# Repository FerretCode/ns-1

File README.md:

# ns-1

Lo-fi first hardware sampler

# Overview

- Teensy 4.1 based
- 16 Cherry MX switch pads
- 1/4" line in/out
- 3.5mm headphone jack
- 3 rotary encoders for sample editing
- 4 potentiometers for FX control
- Slider for master track volume control
- MicroSD card for loading and exporting samples
- Per-pad looping
- Resampling
- Sampling over USB-C

## Architecture

- The core audio processing functionality is provided by the Teensy 4.1 and its accompanying audio shield (Rev. D)
- Adafruit 1.9" TFT display over SPI
- Line in/out, headphone jack is handled by the audio shield, with volume control in firmware

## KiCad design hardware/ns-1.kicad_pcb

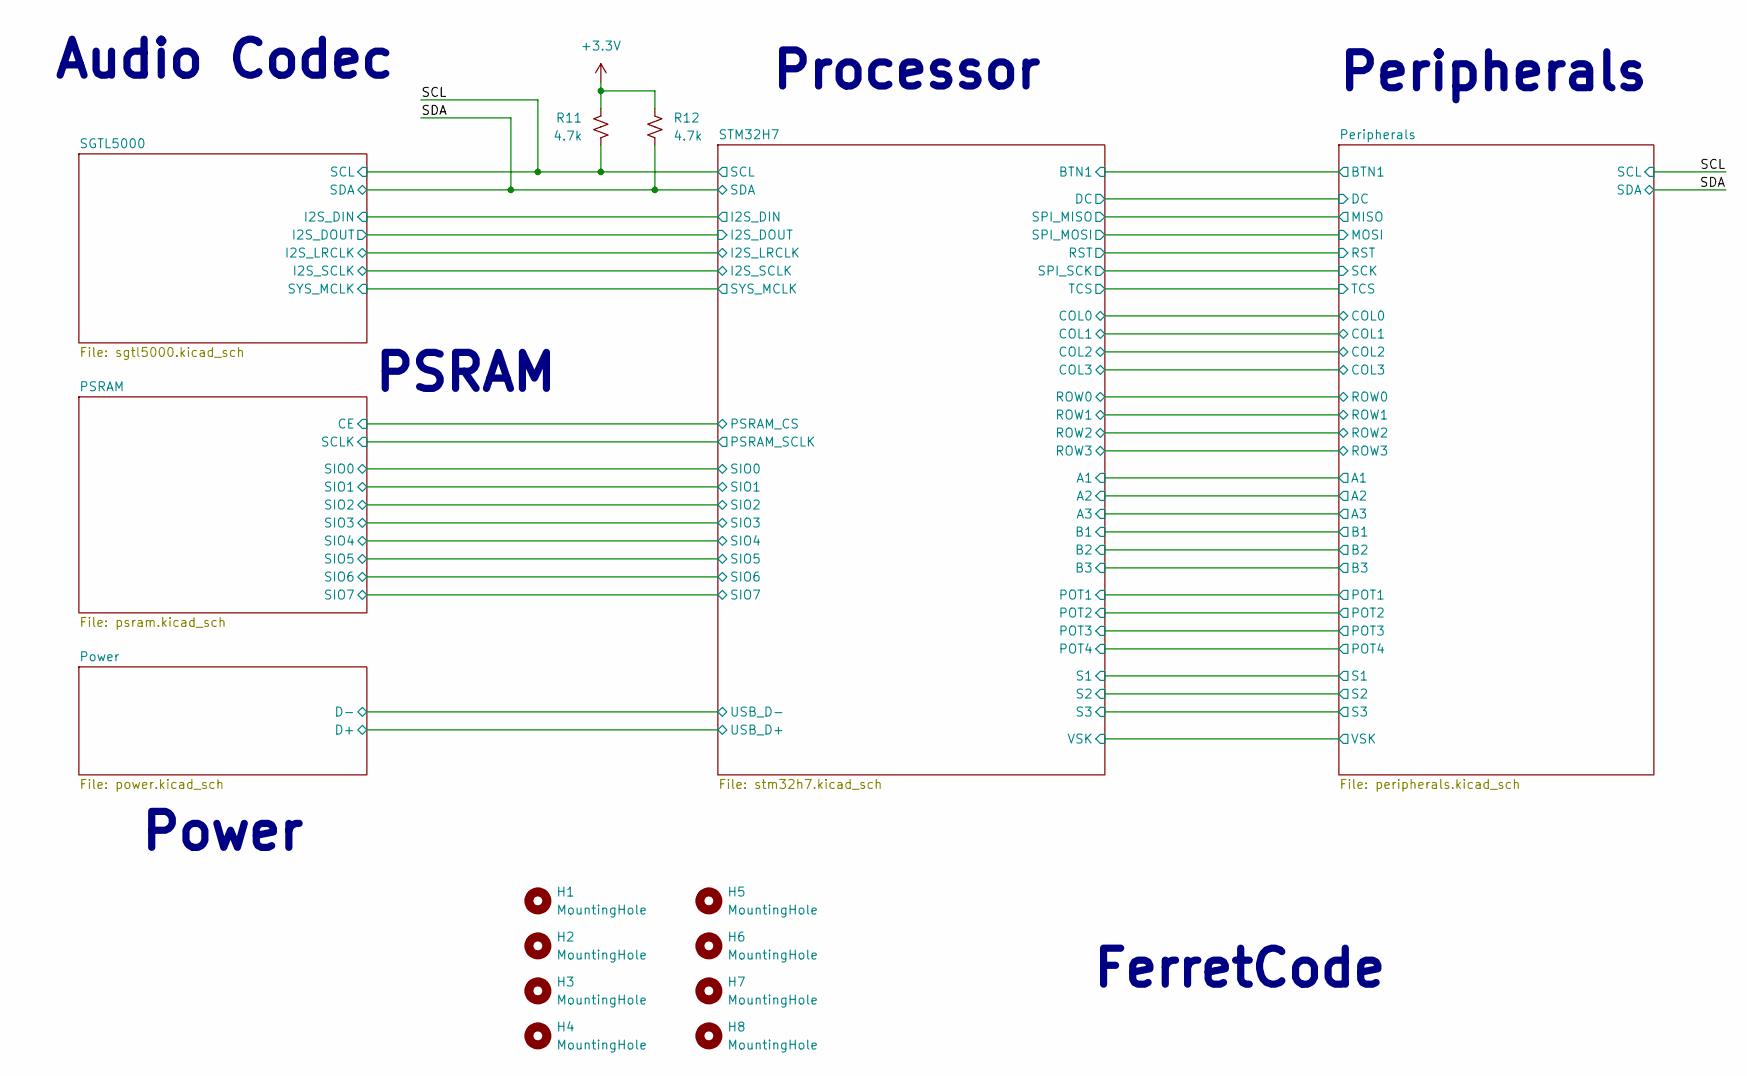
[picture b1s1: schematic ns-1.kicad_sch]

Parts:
H1, H2, H3, H4: MountingHole; MountingHole_2.5mm
H5, H6, H7, H8: MountingHole; MountingHole_4.5mm
R11, R12: 4.7k; R_0402_1005Metric; LCSC PN C25900

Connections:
+3.3V: R11.1, R12.1; also elsewhere on the board
/SCL: R11.2; also elsewhere on the board
/SDA: R12.2; also elsewhere on the board

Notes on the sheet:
Processor
FerretCode
Power
Peripherals
Audio Codec
PSRAM

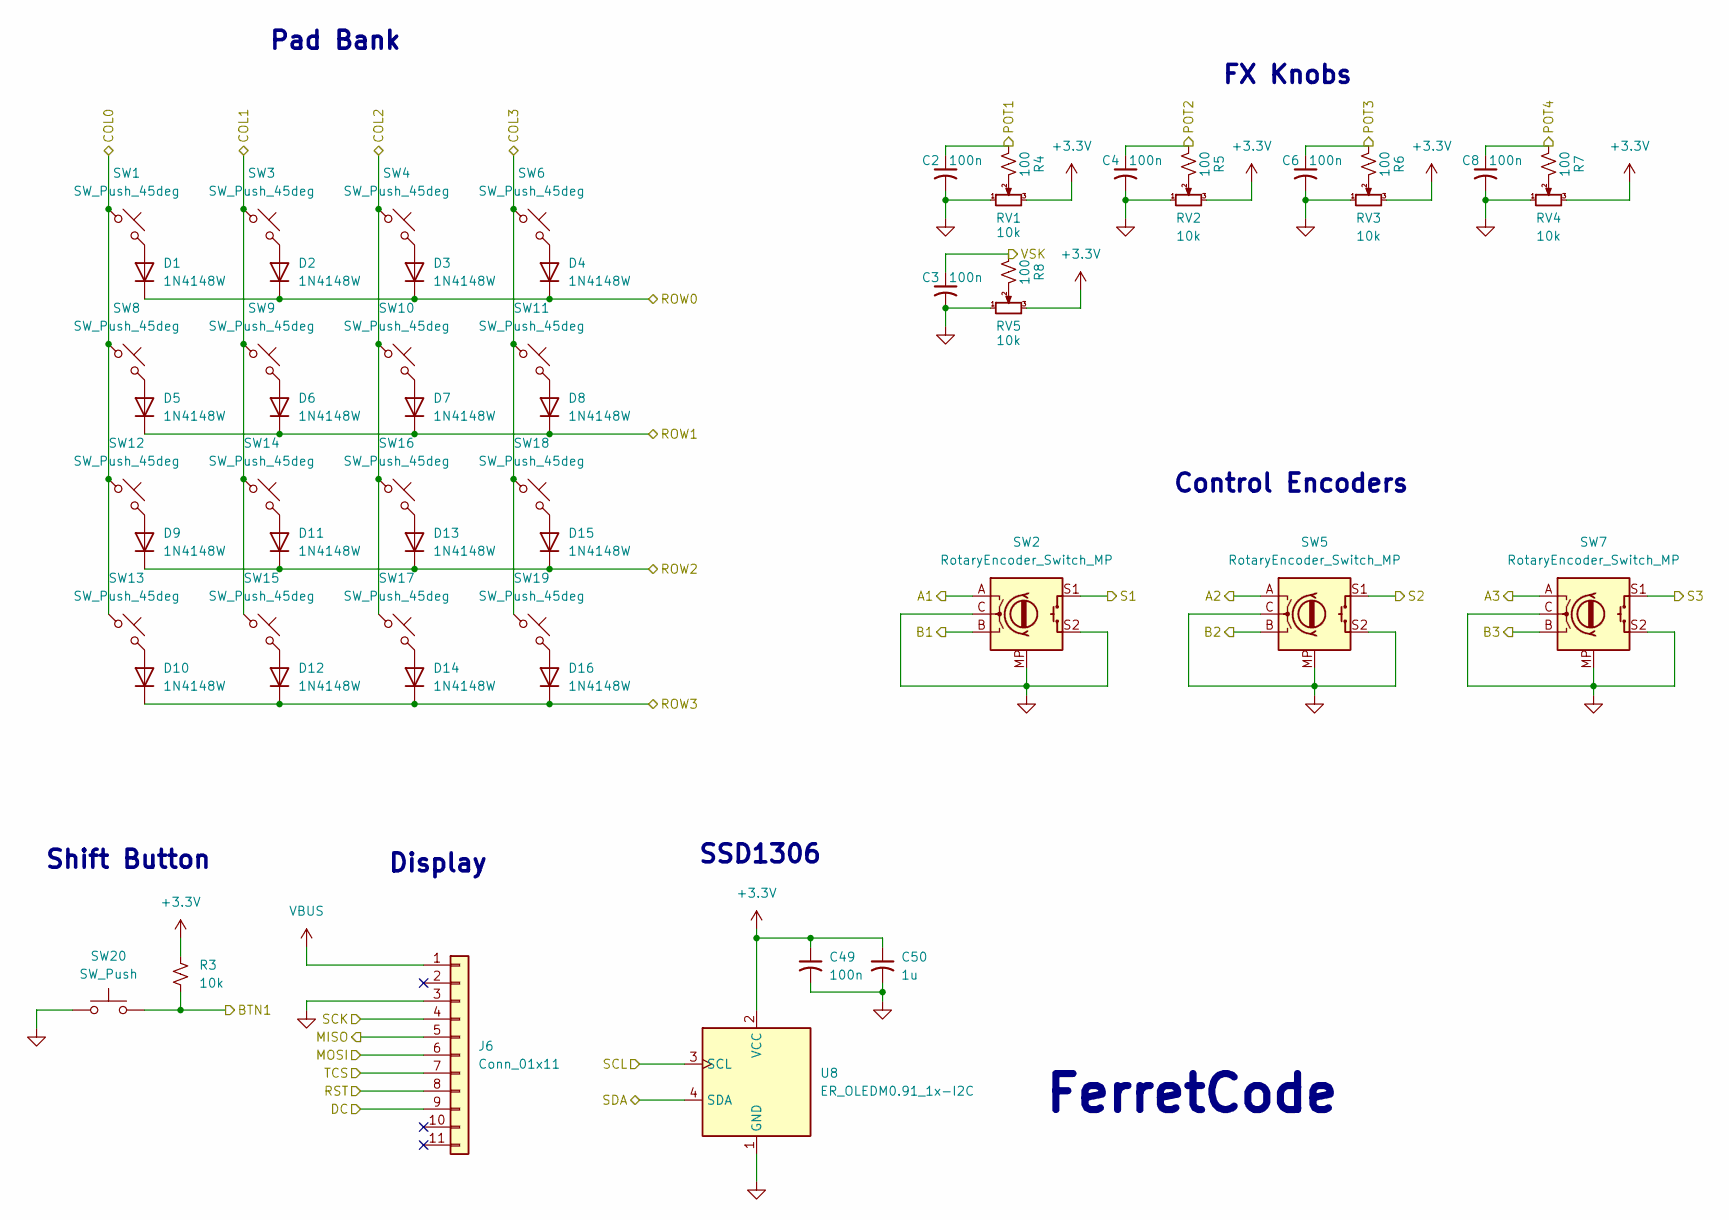
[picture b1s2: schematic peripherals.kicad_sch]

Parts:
C2, C3, C4, C6: 100n; C_0402_1005Metric; LCSC PN C22435941
C8, C49: 100n; C_0402_1005Metric; LCSC PN C1525
C50: 1u; C_0402_1005Metric; LCSC PN C52923
D1, D2, D3, D4, D5, D6, D7, D8, D9, D10, D11, D12, D13, D14, D15, D16: 1N4148W; D_SOD-123; LCSC PN C917030
J6: Conn_01x11; PinHeader_1x11_P2.54mm_Vertical
R3: 10k; R_0603_1608Metric; LCSC PN C25804
R4, R5, R6, R7, R8: 100; R_0603_1608Metric; LCSC PN C122970
RV1, RV2, RV3, RV4, RV5: 10k; Potentiometer_Alps_RK09K_Single_Vertical
SW1, SW3, SW4, SW6, SW8, SW9, SW10, SW11, SW12, SW13, SW14, SW15, SW16, SW17, SW18, SW19: SW_Push_45deg; SW_Cherry_MX_1.00u_PCB
SW2, SW5, SW7: RotaryEncoder_Switch_MP; RotaryEncoder_Alps_EC11E-Switch_Vertical_H20mm
SW20: SW_Push; SW_Cherry_MX_1.00u_PCB
U8: ER_OLEDM0.91_1x-I2C

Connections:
+3.3V: C49.1, C50.1, R3.1, RV1.3, RV2.3, RV3.3, RV4.3, RV5.3, U8.2 (VCC); also elsewhere on the board
/Peripherals/A1: SW2.A; also elsewhere on the board
/Peripherals/A2: SW5.A; also elsewhere on the board
/Peripherals/A3: SW7.A; also elsewhere on the board
/Peripherals/B1: SW2.B; also elsewhere on the board
/Peripherals/B2: SW5.B; also elsewhere on the board
/Peripherals/B3: SW7.B; also elsewhere on the board
/Peripherals/BTN1: R3.2, SW20.2; also elsewhere on the board
/Peripherals/COL0: SW1.1, SW8.1, SW12.1, SW13.1; also elsewhere on the board
/Peripherals/COL1: SW3.1, SW9.1, SW14.1, SW15.1; also elsewhere on the board
/Peripherals/COL2: SW4.1, SW10.1, SW16.1, SW17.1; also elsewhere on the board
/Peripherals/COL3: SW6.1, SW11.1, SW18.1, SW19.1; also elsewhere on the board
/Peripherals/DC: J6.9; also elsewhere on the board
/Peripherals/MISO: J6.5; also elsewhere on the board
/Peripherals/MOSI: J6.6; also elsewhere on the board
/Peripherals/POT1: C2.1, R4.2; also elsewhere on the board
/Peripherals/POT2: C4.1, R5.2; also elsewhere on the board
/Peripherals/POT3: C6.1, R6.2; also elsewhere on the board
/Peripherals/POT4: C8.1, R7.2; also elsewhere on the board
/Peripherals/ROW0: D1.1 (K), D2.1 (K), D3.1 (K), D4.1 (K); also elsewhere on the board
/Peripherals/ROW1: D5.1 (K), D6.1 (K), D7.1 (K), D8.1 (K); also elsewhere on the board
/Peripherals/ROW2: D9.1 (K), D11.1 (K), D13.1 (K), D15.1 (K); also elsewhere on the board
/Peripherals/ROW3: D10.1 (K), D12.1 (K), D14.1 (K), D16.1 (K); also elsewhere on the board
/Peripherals/RST: J6.8; also elsewhere on the board
/Peripherals/S1: SW2.S1; also elsewhere on the board
/Peripherals/S2: SW5.S1; also elsewhere on the board
/Peripherals/S3: SW7.S1; also elsewhere on the board
/Peripherals/SCK: J6.4; also elsewhere on the board
/Peripherals/TCS: J6.7; also elsewhere on the board
/Peripherals/VSK: C3.1, R8.2; also elsewhere on the board
/SCL: U8.3 (SCL); also elsewhere on the board
/SDA: U8.4 (SDA); also elsewhere on the board
GND: C2.2, C3.2, C4.2, C6.2, C8.2, C49.2, C50.2, J6.3, RV1.1, RV2.1, RV3.1, RV4.1, RV5.1, SW2.C, SW2.MP, SW2.S2, SW5.C, SW5.MP, SW5.S2, SW7.C, SW7.MP, SW7.S2, SW20.1, U8.1 (GND); also elsewhere on the board
unnamed: D1.2 (A), SW1.2
unnamed: D2.2 (A), SW3.2
unnamed: D3.2 (A), SW4.2
unnamed: D4.2 (A), SW6.2
unnamed: D5.2 (A), SW8.2
unnamed: D6.2 (A), SW9.2
unnamed: D7.2 (A), SW10.2
unnamed: D8.2 (A), SW11.2
unnamed: D9.2 (A), SW12.2
unnamed: D10.2 (A), SW13.2
unnamed: D11.2 (A), SW14.2
unnamed: D12.2 (A), SW15.2
unnamed: D13.2 (A), SW16.2
unnamed: D14.2 (A), SW17.2
unnamed: D15.2 (A), SW18.2
unnamed: D16.2 (A), SW19.2
unnamed: R4.1, RV1.2
unnamed: R5.1, RV2.2
unnamed: R6.1, RV3.2
unnamed: R7.1, RV4.2
unnamed: R8.1, RV5.2
VBUS: J6.1; also elsewhere on the board

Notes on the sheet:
FerretCode
FX Knobs
Display
SSD1306
Pad Bank
Control Encoders
Shift Button

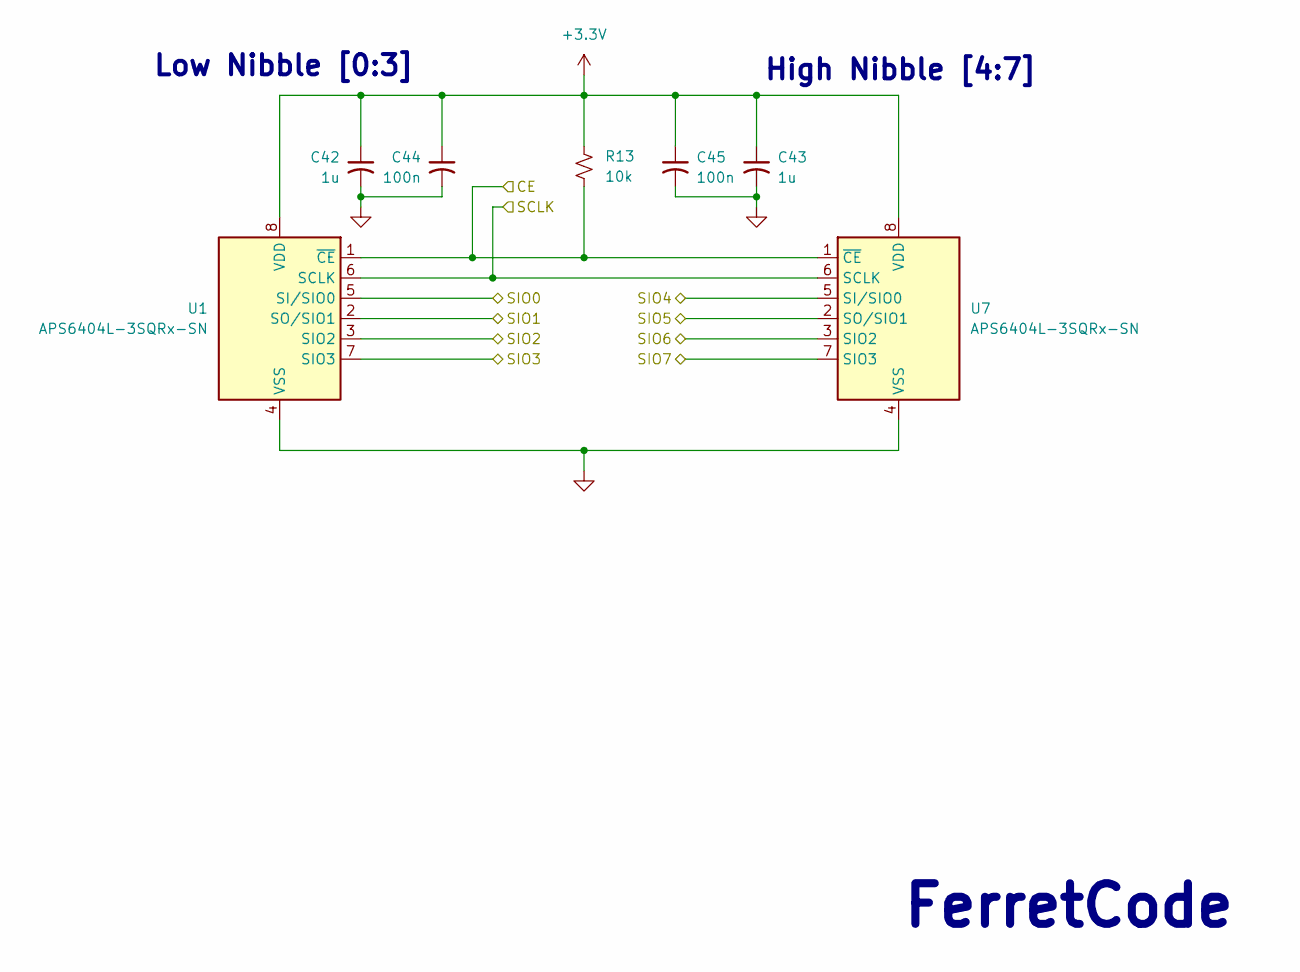
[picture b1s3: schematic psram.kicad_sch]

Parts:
C42, C43: 1u; C_0402_1005Metric; LCSC PN C52923
C44, C45: 100n; C_0402_1005Metric; LCSC PN C1525
R13: 10k; R_0402_1005Metric; LCSC PN C25744
U1, U7: APS6404L-3SQRx-SN; SOIC-8_3.9x4.9mm_P1.27mm; LCSC PN C3028887

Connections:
+3.3V: C42.1, C43.1, C44.1, C45.1, R13.1, U1.8 (VDD), U7.8 (VDD); also elsewhere on the board
/PSRAM/CE: R13.2, U1.1 (~CE), U7.1 (~CE); also elsewhere on the board
/PSRAM/SCLK: U1.6 (SCLK), U7.6 (SCLK); also elsewhere on the board
/PSRAM/SIO0: U1.5 (SI/SIO0); also elsewhere on the board
/PSRAM/SIO1: U1.2 (SO/SIO1); also elsewhere on the board
/PSRAM/SIO2: U1.3 (SIO2); also elsewhere on the board
/PSRAM/SIO3: U1.7 (SIO3); also elsewhere on the board
/PSRAM/SIO4: U7.5 (SI/SIO0); also elsewhere on the board
/PSRAM/SIO5: U7.2 (SO/SIO1); also elsewhere on the board
/PSRAM/SIO6: U7.3 (SIO2); also elsewhere on the board
/PSRAM/SIO7: U7.7 (SIO3); also elsewhere on the board
GND: C42.2, C43.2, C44.2, C45.2, U1.4 (VSS), U7.4 (VSS); also elsewhere on the board

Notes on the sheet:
FerretCode
Low Nibble [0:3]
High Nibble [4:7]

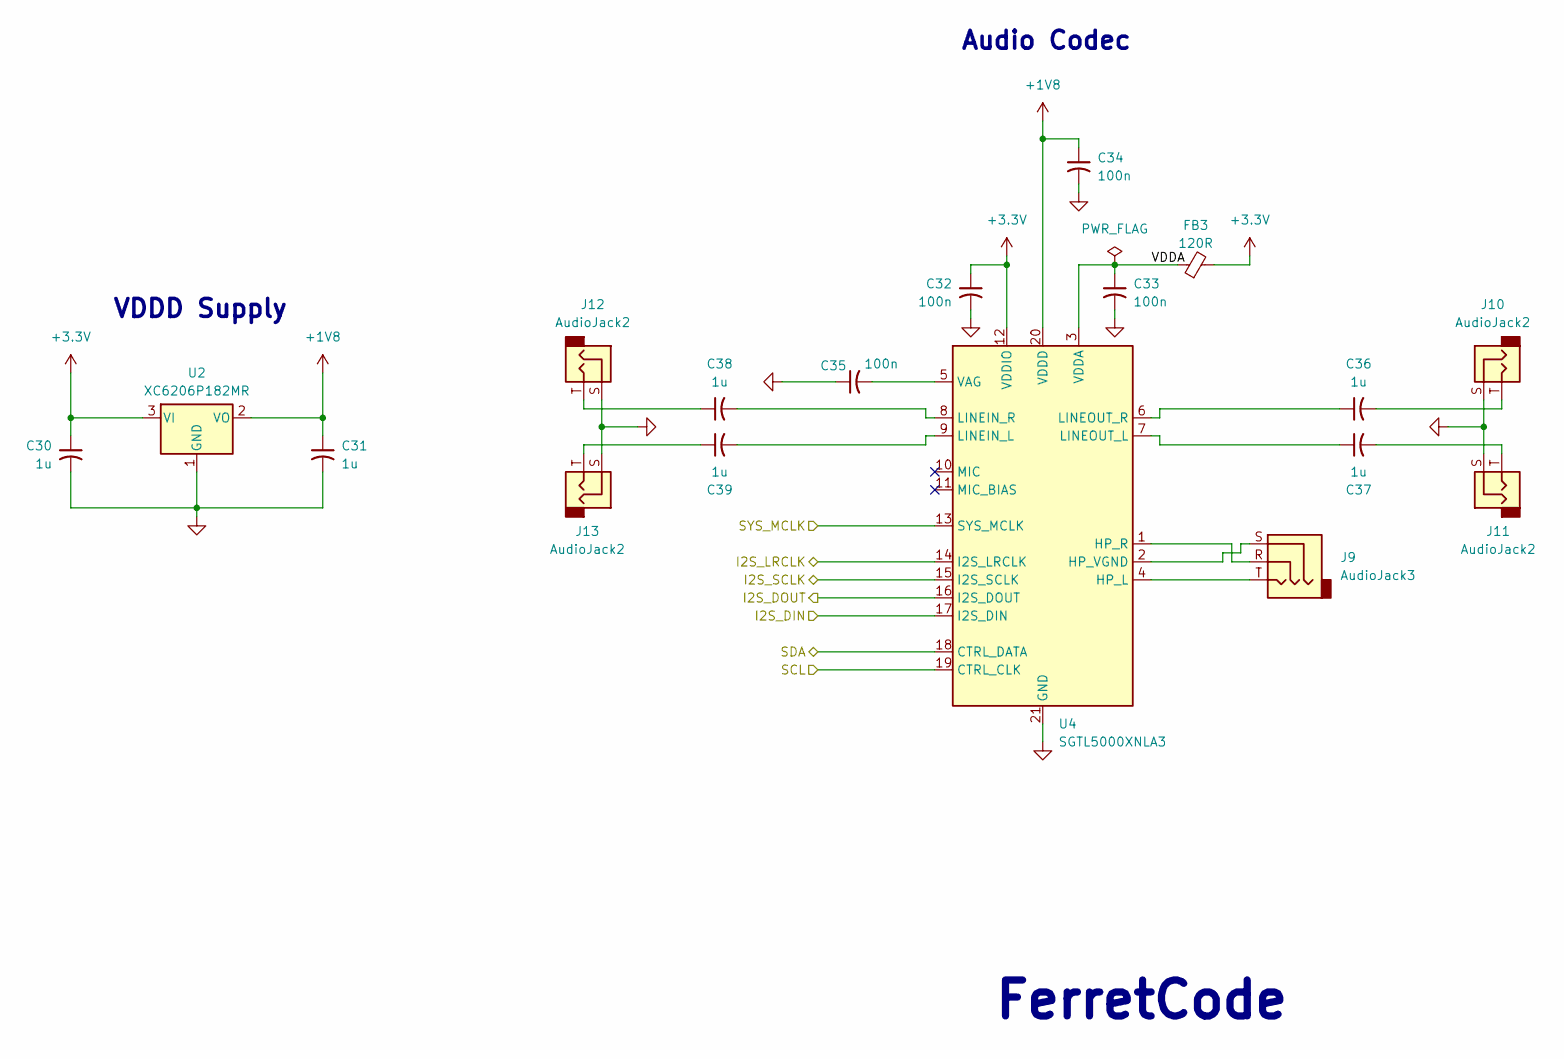
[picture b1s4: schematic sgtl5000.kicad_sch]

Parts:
C30, C31, C36, C37, C38, C39: 1u; C_0402_1005Metric; LCSC PN C52923
C32, C33, C34, C35: 100n; C_0402_1005Metric; LCSC PN C1525
FB3: 120R; L_0603_1608Metric; LCSC PN C14709
J9: AudioJack3; Jack_3.5mm_CUI_SJ-3523-SMT_Horizontal
J10, J11, J12, J13: AudioJack2; Jack_6.35mm_Neutrik_NRJ4HF_Horizontal
U2: XC6206P182MR; SOT-23-3; LCSC PN C347373
U4: SGTL5000XNLA3; QFN-20-1EP_3x3mm_P0.4mm_EP1.65x1.65mm; LCSC PN C2651833

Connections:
+1V8: C31.1, C34.1, U2.2 (VO), U4.20 (VDDD)
+3.3V: C30.1, C32.1, FB3.2, U2.3 (VI), U4.12 (VDDIO); also elsewhere on the board
/SCL: U4.19 (CTRL_CLK); also elsewhere on the board
/SDA: U4.18 (CTRL_DATA); also elsewhere on the board
/SGTL5000/I2S_DIN: U4.17 (I2S_DIN); also elsewhere on the board
/SGTL5000/I2S_DOUT: U4.16 (I2S_DOUT); also elsewhere on the board
/SGTL5000/I2S_LRCLK: U4.14 (I2S_LRCLK); also elsewhere on the board
/SGTL5000/I2S_SCLK: U4.15 (I2S_SCLK); also elsewhere on the board
/SGTL5000/SYS_MCLK: U4.13 (SYS_MCLK); also elsewhere on the board
/SGTL5000/VDDA: C33.1, FB3.1, U4.3 (VDDA)
GND: C30.2, C31.2, C32.2, C33.2, C34.2, C35.1, J10.S, J11.S, J12.S, J13.S, U2.1 (GND), U4.21 (GND); also elsewhere on the board
unnamed: C36.2, J10.T
unnamed: C37.2, J11.T
unnamed: C38.1, J12.T
unnamed: C39.1, J13.T
unnamed: J9.T, U4.4 (HP_L)
unnamed: J9.R, U4.1 (HP_R)
unnamed: J9.S, U4.2 (HP_VGND)
unnamed: C39.2, U4.9 (LINEIN_L)
unnamed: C38.2, U4.8 (LINEIN_R)
unnamed: C37.1, U4.7 (LINEOUT_L)
unnamed: C36.1, U4.6 (LINEOUT_R)
unnamed: C35.2, U4.5 (VAG)

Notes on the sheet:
VDDD Supply
Audio Codec
FerretCode

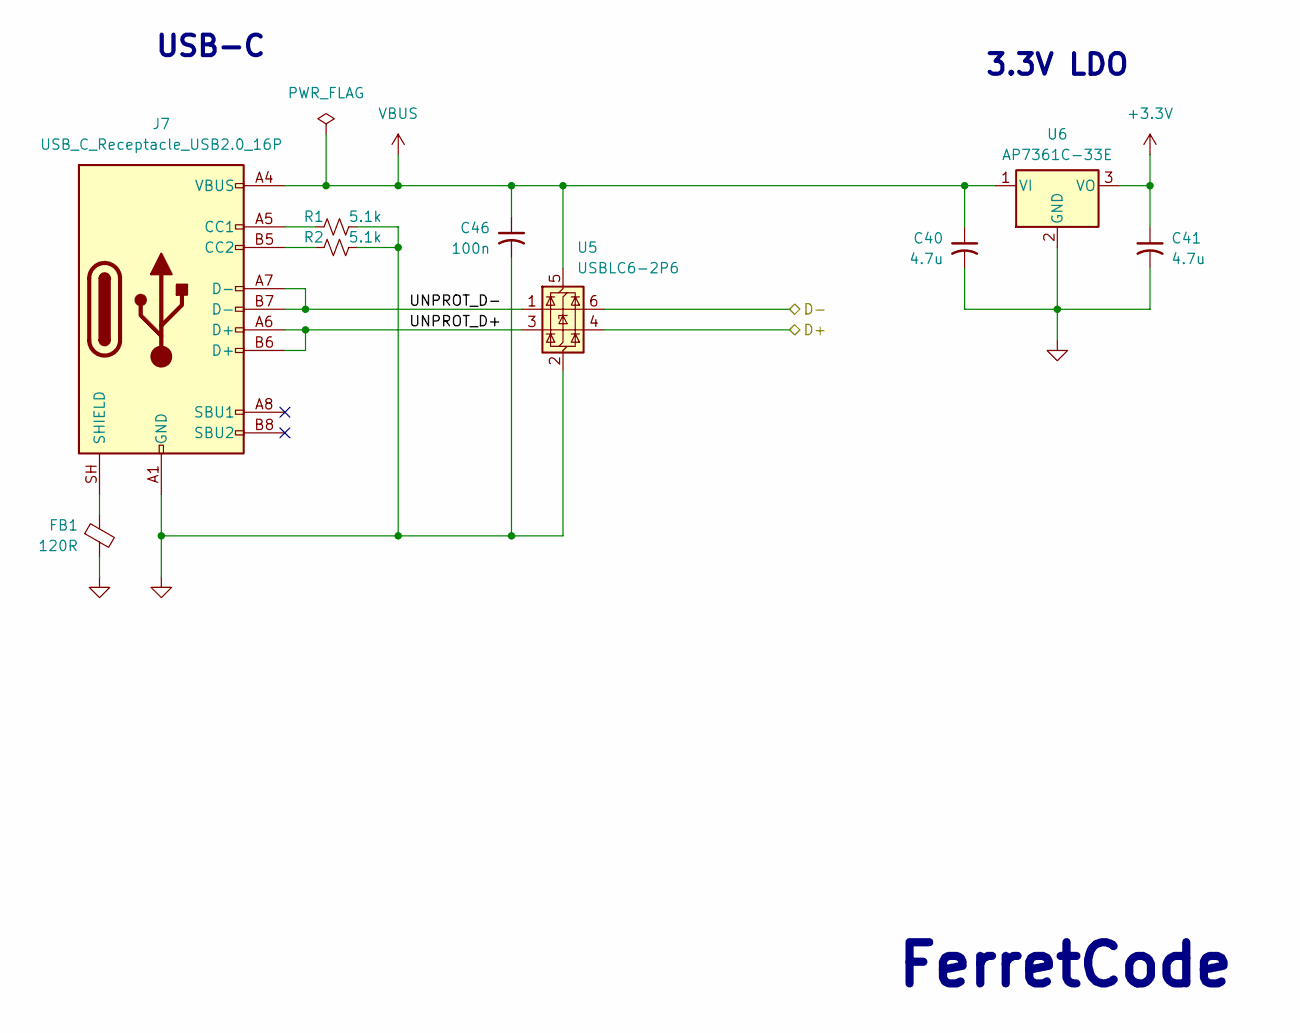
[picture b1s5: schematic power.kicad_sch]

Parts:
C40, C41: 4.7u; C_0805_2012Metric; LCSC PN C1779
C46: 100n; C_0402_1005Metric; LCSC PN C1525
FB1: 120R; L_0805_2012Metric; LCSC PN C2943443
J7: USB_C_Receptacle_USB2.0_16P; USB_C_Receptacle_HRO_TYPE-C-31-M-12; LCSC PN C165948
R1, R2: 5.1k; R_0603_1608Metric; LCSC PN C23186
U5: USBLC6-2P6; SOT-666; LCSC PN C2827693
U6: AP7361C-33E; SOT-223-3_TabPin2; LCSC PN C500795

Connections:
+3.3V: C41.1, U6.3 (VO); also elsewhere on the board
/Power/D+: U5.4 (I/O2); also elsewhere on the board
/Power/D-: U5.6 (I/O1); also elsewhere on the board
/Power/UNPROT_D+: J7.A6 (D+), J7.B6 (D+), U5.3 (I/O2)
/Power/UNPROT_D-: J7.A7 (D-), J7.B7 (D-), U5.1 (I/O1)
GND: C40.2, C41.2, C46.2, FB1.2, J7.A1 (GND), J7.A12 (GND), J7.B1 (GND), J7.B12 (GND), R1.2, R2.2, U5.2 (GND), U6.2 (GND); also elsewhere on the board
unnamed: J7.A5 (CC1), R1.1
unnamed: J7.B5 (CC2), R2.1
unnamed: FB1.1, J7.SH (SHIELD)
VBUS: C40.1, C46.1, J7.A4 (VBUS), J7.A9 (VBUS), J7.B4 (VBUS), J7.B9 (VBUS), U5.5 (VBUS), U6.1 (VI); also elsewhere on the board

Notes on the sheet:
3.3V LDO
USB-C
FerretCode

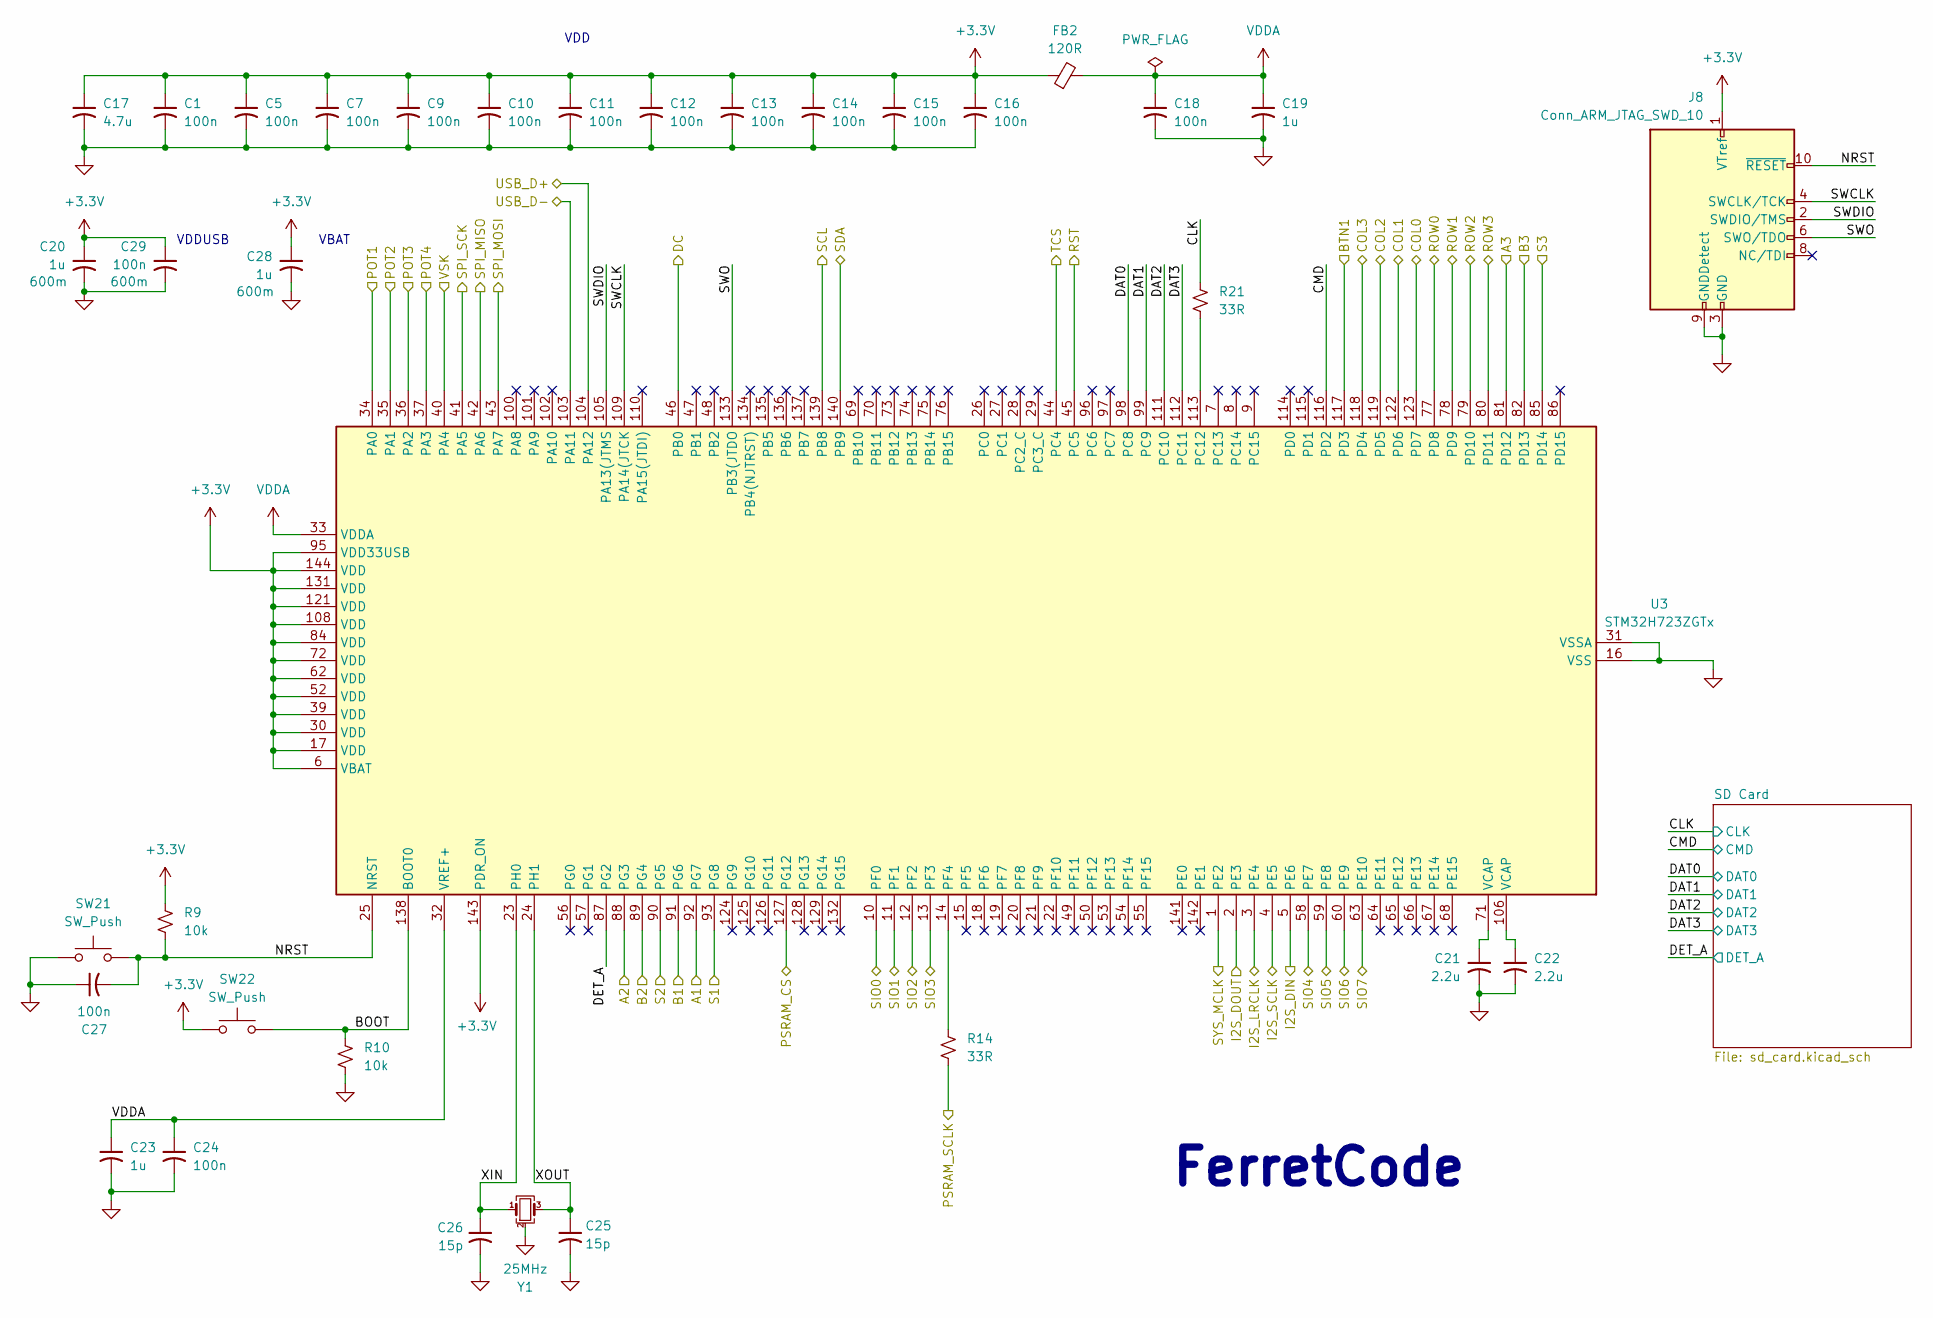
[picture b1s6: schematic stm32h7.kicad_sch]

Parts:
C1, C5, C7, C9, C10, C11, C12, C13, C14, C15, C16, C18, C24, C27, C29: 100n; C_0402_1005Metric; LCSC PN C1525
C17: 4.7u; C_0402_1005Metric; LCSC PN C23733
C19, C20, C23, C28: 1u; C_0402_1005Metric; LCSC PN C52923
C21, C22: 2.2u; C_0603_1608Metric; LCSC PN C23630
C25, C26: 15p; C_0402_1005Metric; LCSC PN C1548
FB2: 120R; L_0603_1608Metric; LCSC PN C14709
J8: Conn_ARM_JTAG_SWD_10; PinHeader_2x05_P1.27mm_Vertical_SMD; LCSC PN C598540
R9, R10: 10k; R_0402_1005Metric; LCSC PN C25744
R14, R21: 33R; R_0402_1005Metric; LCSC PN C25105
SW21, SW22: SW_Push; SW_Push_SPST_NO_Alps_SKRK; LCSC PN C202388
U3: STM32H723ZGTx; LQFP-144_20x20mm_P0.5mm; LCSC PN C730146
Y1: 25MHz; Crystal_SMD_3225-4Pin_3.2x2.5mm; LCSC PN C9006

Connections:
+3.3V: C1.1, C5.1, C7.1, C9.1, C10.1, C11.1, C12.1, C13.1, C14.1, C15.1, C16.1, C17.1, C20.1, C28.1, C29.1, FB2.1, J8.1 (VTref), R9.1, SW22.1, U3.6 (VBAT), U3.17 (VDD), U3.30 (VDD), U3.39 (VDD), U3.52 (VDD), U3.62 (VDD), U3.72 (VDD), U3.84 (VDD), U3.95 (VDD33USB), U3.108 (VDD), U3.121 (VDD), U3.131 (VDD), U3.143 (PDR_ON), U3.144 (VDD); also elsewhere on the board
/PSRAM/CE: U3.127 (PG12); also elsewhere on the board
/PSRAM/SCLK: R14.2; also elsewhere on the board
/PSRAM/SIO0: U3.10 (PF0); also elsewhere on the board
/PSRAM/SIO1: U3.11 (PF1); also elsewhere on the board
/PSRAM/SIO2: U3.12 (PF2); also elsewhere on the board
/PSRAM/SIO3: U3.13 (PF3); also elsewhere on the board
/PSRAM/SIO4: U3.58 (PE7); also elsewhere on the board
/PSRAM/SIO5: U3.59 (PE8); also elsewhere on the board
/PSRAM/SIO6: U3.60 (PE9); also elsewhere on the board
/PSRAM/SIO7: U3.63 (PE10); also elsewhere on the board
/Peripherals/A1: U3.92 (PG7); also elsewhere on the board
/Peripherals/A2: U3.88 (PG3); also elsewhere on the board
/Peripherals/A3: U3.81 (PD12); also elsewhere on the board
/Peripherals/B1: U3.91 (PG6); also elsewhere on the board
/Peripherals/B2: U3.89 (PG4); also elsewhere on the board
/Peripherals/B3: U3.82 (PD13); also elsewhere on the board
/Peripherals/BTN1: U3.117 (PD3); also elsewhere on the board
/Peripherals/COL0: U3.123 (PD7); also elsewhere on the board
/Peripherals/COL1: U3.122 (PD6); also elsewhere on the board
/Peripherals/COL2: U3.119 (PD5); also elsewhere on the board
/Peripherals/COL3: U3.118 (PD4); also elsewhere on the board
/Peripherals/DC: U3.46 (PB0); also elsewhere on the board
/Peripherals/MISO: U3.42 (PA6); also elsewhere on the board
/Peripherals/MOSI: U3.43 (PA7); also elsewhere on the board
/Peripherals/POT1: U3.34 (PA0); also elsewhere on the board
/Peripherals/POT2: U3.35 (PA1); also elsewhere on the board
/Peripherals/POT3: U3.36 (PA2); also elsewhere on the board
/Peripherals/POT4: U3.37 (PA3); also elsewhere on the board
/Peripherals/ROW0: U3.77 (PD8); also elsewhere on the board
/Peripherals/ROW1: U3.78 (PD9); also elsewhere on the board
/Peripherals/ROW2: U3.79 (PD10); also elsewhere on the board
/Peripherals/ROW3: U3.80 (PD11); also elsewhere on the board
/Peripherals/RST: U3.45 (PC5); also elsewhere on the board
/Peripherals/S1: U3.93 (PG8); also elsewhere on the board
/Peripherals/S2: U3.90 (PG5); also elsewhere on the board
/Peripherals/S3: U3.85 (PD14); also elsewhere on the board
/Peripherals/SCK: U3.41 (PA5); also elsewhere on the board
/Peripherals/TCS: U3.44 (PC4); also elsewhere on the board
/Peripherals/VSK: U3.40 (PA4); also elsewhere on the board
/Power/D+: U3.104 (PA12); also elsewhere on the board
/Power/D-: U3.103 (PA11); also elsewhere on the board
/SCL: U3.139 (PB8); also elsewhere on the board
/SDA: U3.140 (PB9); also elsewhere on the board
/SGTL5000/I2S_DIN: U3.5 (PE6); also elsewhere on the board
/SGTL5000/I2S_DOUT: U3.2 (PE3); also elsewhere on the board
/SGTL5000/I2S_LRCLK: U3.3 (PE4); also elsewhere on the board
/SGTL5000/I2S_SCLK: U3.4 (PE5); also elsewhere on the board
/SGTL5000/SYS_MCLK: U3.1 (PE2); also elsewhere on the board
/STM32H7/BOOT: R10.1, SW22.2, U3.138 (BOOT0)
/STM32H7/CLK: R21.1; also elsewhere on the board
/STM32H7/CMD: U3.116 (PD2); also elsewhere on the board
/STM32H7/DAT0: U3.98 (PC8); also elsewhere on the board
/STM32H7/DAT1: U3.99 (PC9); also elsewhere on the board
/STM32H7/DAT2: U3.111 (PC10); also elsewhere on the board
/STM32H7/DAT3: U3.112 (PC11); also elsewhere on the board
/STM32H7/DET_A: U3.87 (PG2); also elsewhere on the board
/STM32H7/NRST: C27.2, J8.10 (~RESET), R9.2, SW21.2, U3.25 (NRST)
/STM32H7/SWCLK: J8.4 (SWCLK/TCK), U3.109 (PA14(JTCK)
/STM32H7/SWDIO: J8.2 (SWDIO/TMS), U3.105 (PA13(JTMS)
/STM32H7/SWO: J8.6 (SWO/TDO), U3.133 (PB3(JTDO)
/STM32H7/XIN: C26.1, U3.23 (PH0), Y1.1
/STM32H7/XOUT: C25.1, U3.24 (PH1), Y1.3
GND: C1.2, C5.2, C7.2, C9.2, C10.2, C11.2, C12.2, C13.2, C14.2, C15.2, C16.2, C17.2, C18.2, C19.2, C20.2, C21.2, C22.2, C23.2, C24.2, C25.2, C26.2, C27.1, C28.2, C29.2, J8.3 (GND), J8.5 (GND), J8.9 (GNDDetect), R10.2, SW21.1, U3.16 (VSS), U3.31 (VSSA), U3.38 (VSS), U3.51 (VSS), U3.61 (VSS), U3.83 (VSS), U3.94 (VSS), U3.107 (VSS), U3.120 (VSS), U3.130 (VSS), Y1.2 (G), Y1.4 (G); also elsewhere on the board
unnamed: C21.1, U3.71 (VCAP)
unnamed: C22.1, U3.106 (VCAP)
unnamed: R21.2, U3.113 (PC12)
unnamed: R14.1, U3.14 (PF4)
VDDA: C18.1, C19.1, C23.1, C24.1, FB2.2, U3.32 (VREF+), U3.33 (VDDA)

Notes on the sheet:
VDDUSB
VBAT
VDD
FerretCode

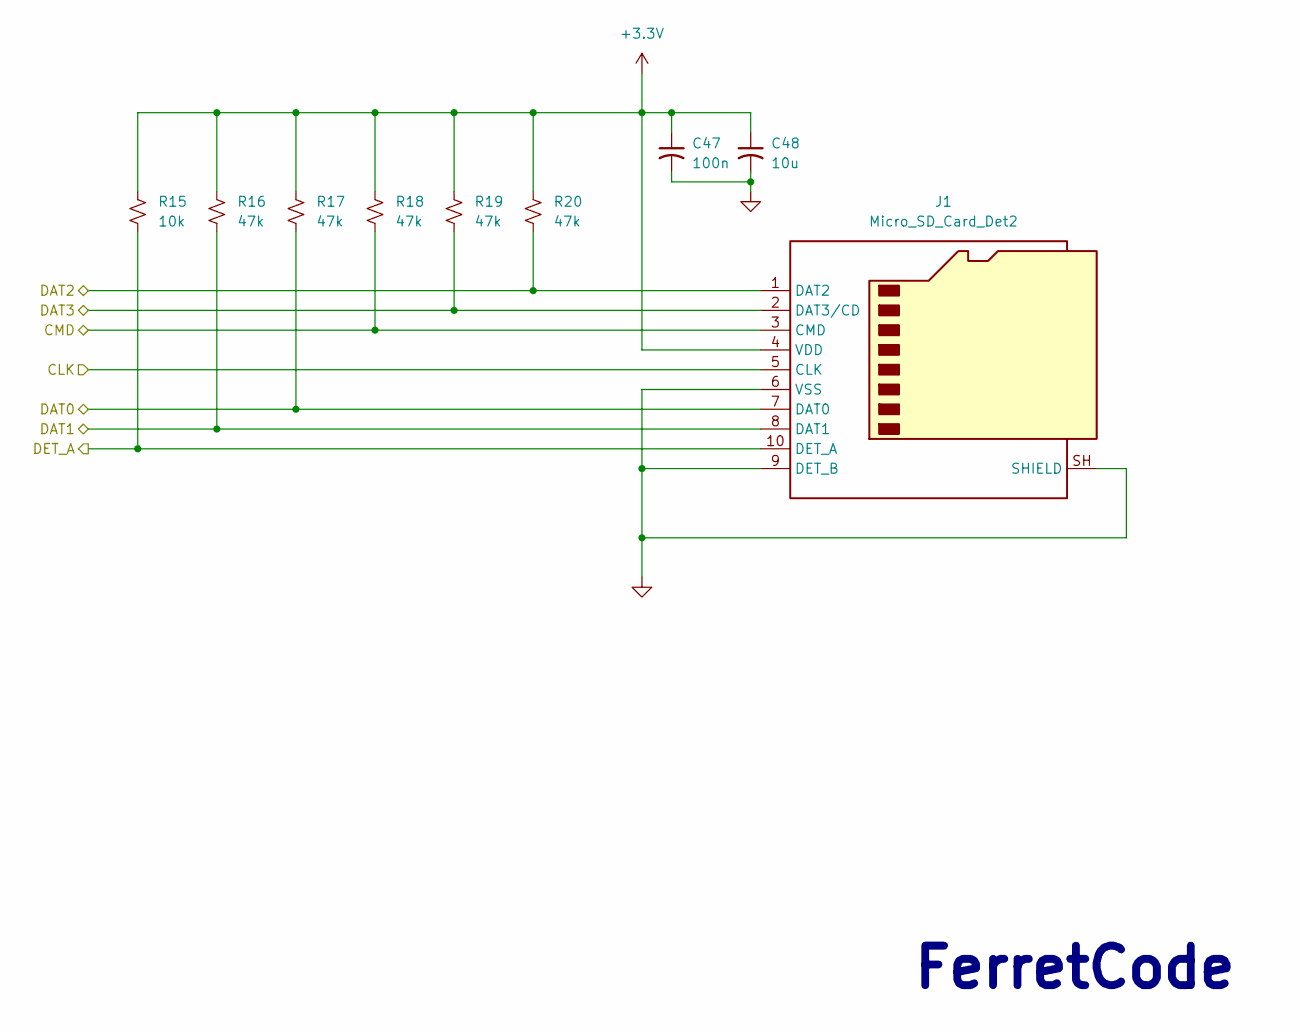
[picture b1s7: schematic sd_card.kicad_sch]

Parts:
C47: 100n; C_0402_1005Metric; LCSC PN C1525
C48: 10u; C_0603_1608Metric; LCSC PN C96446
J1: Micro_SD_Card_Det2; microSD_HC_Hirose_DM3AT-SF-PEJM5; LCSC PN C114218
R15: 10k; R_0402_1005Metric; LCSC PN C25744
R16, R17, R18, R19, R20: 47k; R_0402_1005Metric; LCSC PN C25792

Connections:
+3.3V: C47.1, C48.1, J1.4 (VDD), R15.1, R16.1, R17.1, R18.1, R19.1, R20.1; also elsewhere on the board
/STM32H7/CLK: J1.5 (CLK); also elsewhere on the board
/STM32H7/CMD: J1.3 (CMD), R18.2; also elsewhere on the board
/STM32H7/DAT0: J1.7 (DAT0), R17.2; also elsewhere on the board
/STM32H7/DAT1: J1.8 (DAT1), R16.2; also elsewhere on the board
/STM32H7/DAT2: J1.1 (DAT2), R20.2; also elsewhere on the board
/STM32H7/DAT3: J1.2 (DAT3/CD), R19.2; also elsewhere on the board
/STM32H7/DET_A: J1.10 (DET_A), R15.2; also elsewhere on the board
GND: C47.2, C48.2, J1.6 (VSS), J1.9 (DET_B), J1.SH (SHIELD); also elsewhere on the board

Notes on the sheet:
FerretCode
